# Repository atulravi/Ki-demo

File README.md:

# Ki-demo
Project files for KiCad demo and stencil export and SMD learning by Atul Ravi alias ESC crasci

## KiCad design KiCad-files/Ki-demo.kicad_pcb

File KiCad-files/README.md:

KiCad files for 3D Badge by ESC for learning KiCad and SMD Soldering.

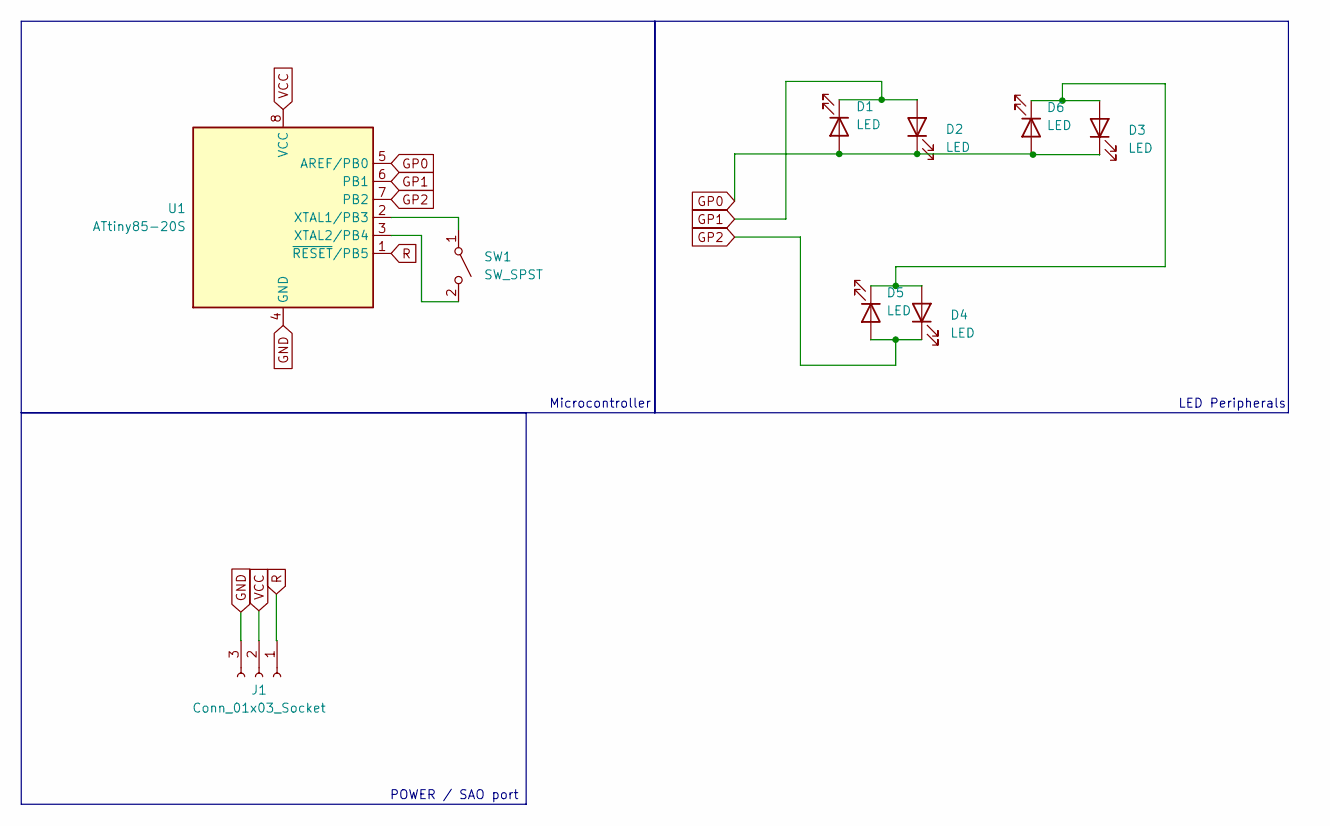
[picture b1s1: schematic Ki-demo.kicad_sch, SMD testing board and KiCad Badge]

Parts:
D1, D3, D4, D5, D6: LED; LED_0805_2012Metric
D2: LED; LED_0805_2012Metric_Pad1.15x1.40mm_HandSolder
J1: Conn_01x03_Socket; PinSocket_1x03_P2.54mm_Vertical
SW1: SW_SPST; SW_SPST_TL3342
U1: ATtiny85-20S; SOIC-8W_5.3x5.3mm_P1.27mm

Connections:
GND: J1.3, U1.4 (GND)
GP0: D1.2 (A), D2.1 (K), D3.1 (K), D6.2 (A), U1.5 (AREF/PB0)
GP1: D1.1 (K), D2.2 (A), U1.6 (PB1)
GP2: D4.1 (K), D5.2 (A), U1.7 (PB2)
unnamed: D3.2 (A), D4.2 (A), D5.1 (K), D6.1 (K)
unnamed: SW1.1 (A), U1.2 (XTAL1/PB3)
unnamed: SW1.2 (B), U1.3 (XTAL2/PB4)
R: J1.1, U1.1 (~RESET/PB5)
VCC: J1.2, U1.8 (VCC)

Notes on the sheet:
Microcontroller
POWER / SAO port
LED Peripherals

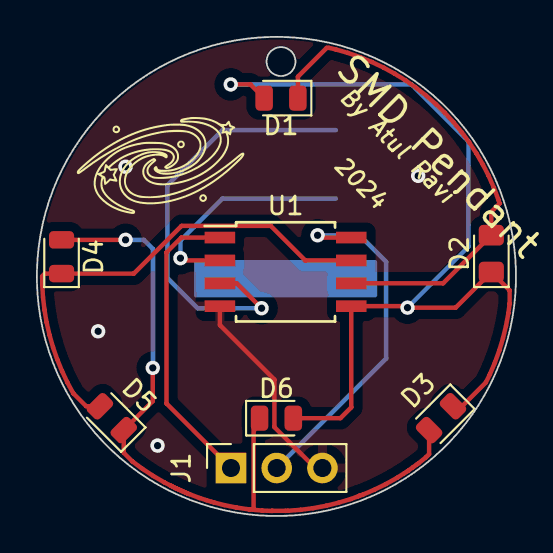
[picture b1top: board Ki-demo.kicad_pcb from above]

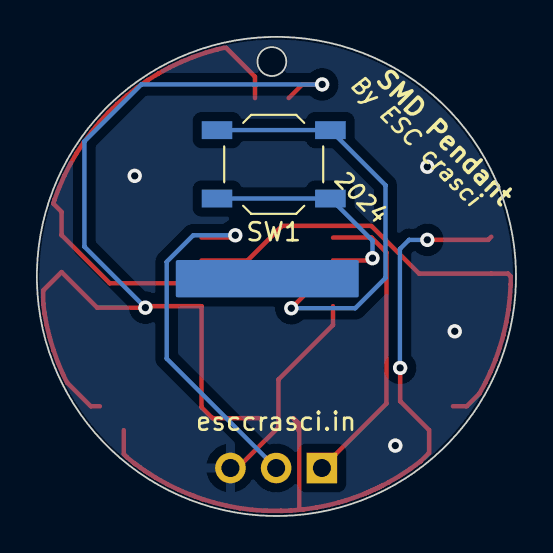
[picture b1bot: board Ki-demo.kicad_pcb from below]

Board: 2 copper layers, 26.6 x 26.6 mm, 10 parts (2 on the bottom side), 9 nets.

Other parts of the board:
HS1: Heatsink_Pad; Badge-Pin Holder

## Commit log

2024-09-01 KiCad files uploaded
